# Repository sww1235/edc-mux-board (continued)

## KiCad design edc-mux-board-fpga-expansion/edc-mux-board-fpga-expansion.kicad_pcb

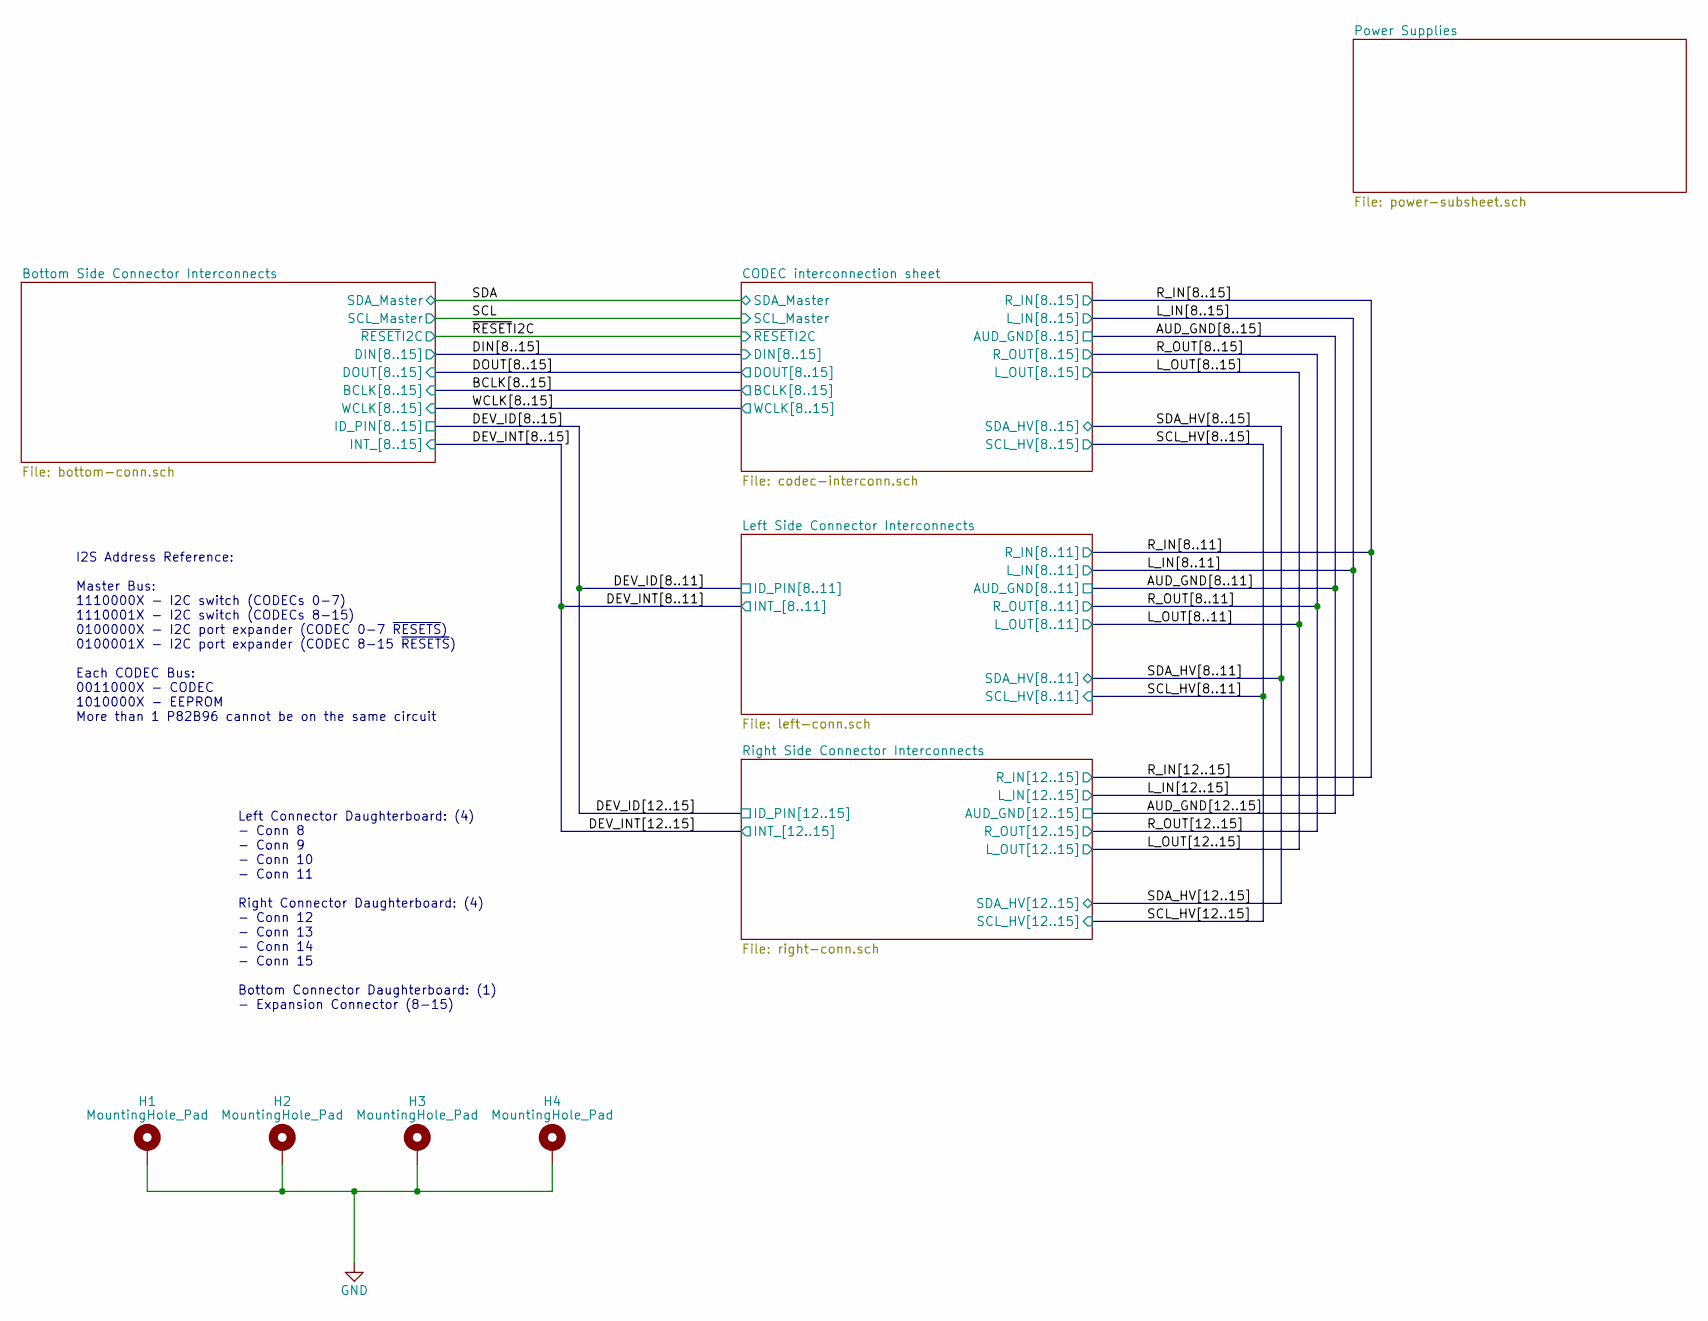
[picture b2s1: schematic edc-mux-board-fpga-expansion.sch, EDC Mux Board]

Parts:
H1, H2, H3, H4: MountingHole_Pad; MountingHole_4.3mm_M4_Pad_Via

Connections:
GND: H1.1, H2.1, H3.1, H4.1; also elsewhere on the board

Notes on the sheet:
Left Connector Daughterboard: (4) - Conn 8 - Conn 9 - Conn 10 - Conn 11 Right Connector Daughterboard: (4) - Conn 12 - Conn 13 - Conn 14 - Conn 15 Bottom Connector Daughterboard: (1) - Expansion Connector (8-15)
I2S Address Reference: Master Bus: 1110000X - I2C switch (CODECs 0-7) 1110001X - I2C switch (CODECs 8-15) 0100000X - I2C port expander (CODEC 0-7 ~RESETS~) 0100001X - I2C port expander (CODEC 8-15 ~RESETS~) Each CODEC Bus: 0011000X - CODEC 1010000X - EEPROM More than 1 P82B96 cannot be on the same 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

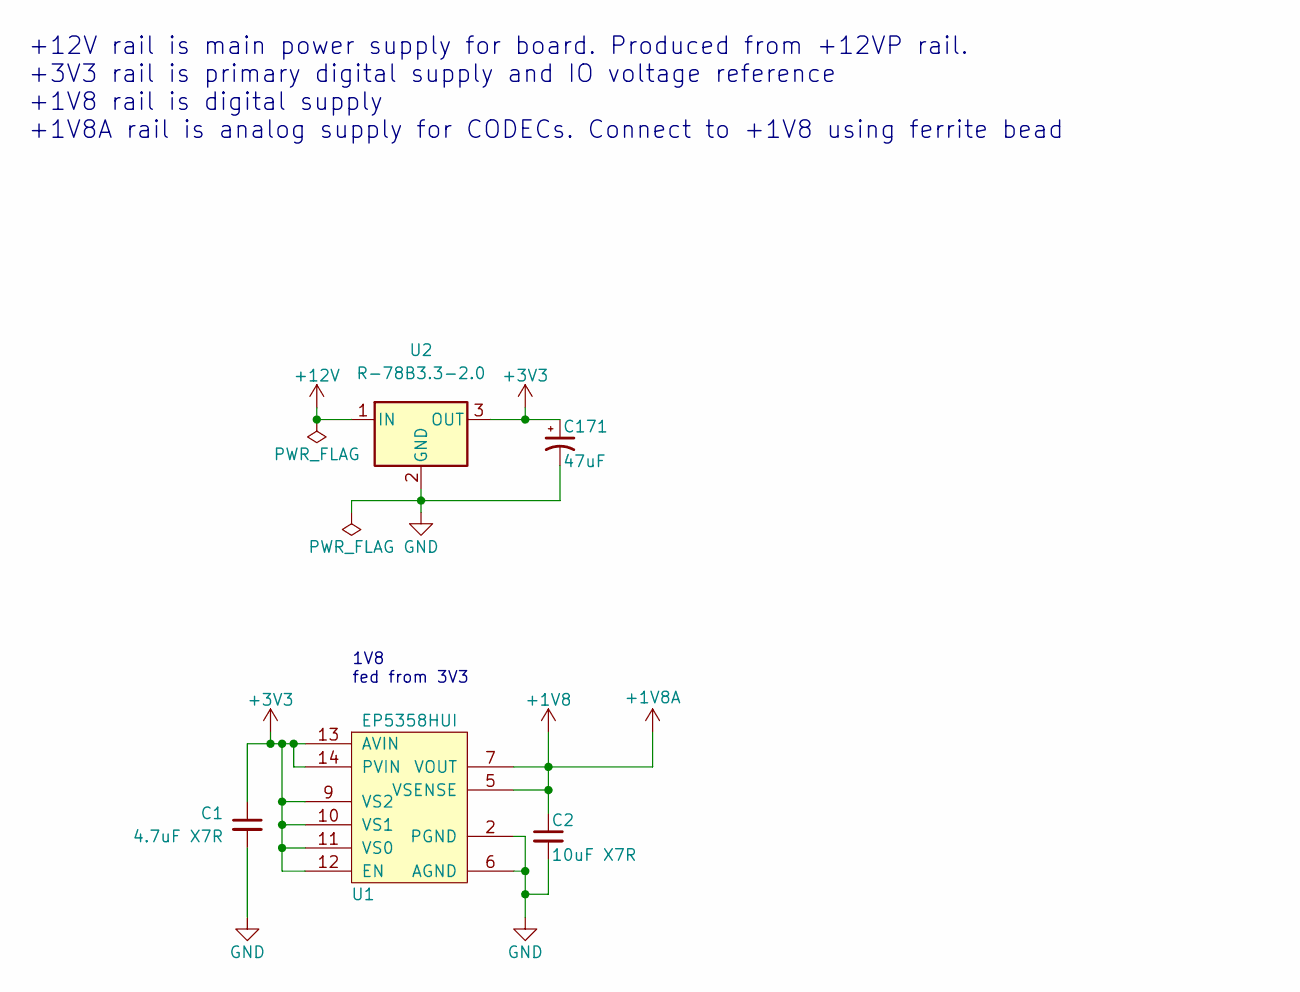
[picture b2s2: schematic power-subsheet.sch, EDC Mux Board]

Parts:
C1: 4.7uF X7R; C_0805_2012Metric; Manufacturers Part Numb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 C2012X7R1E475K125AB
C2: 10uF X7R; C_1206_3216Metric; Manufacturers Part Numb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 C1206C106J3RACAUTO
C171: 47uF; CP_ELEC_8.3x8.3x11.7mm_SMD; Manufacturers Part Numb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 875075555002
U1: EP5358HUI; ENPIRION_QFN16_2.5x2.25x1.1mm-0.4mm; Manufacturers Part Numb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 EP5358HUI
U2: R-78B3.3-2.0; Converter_DCDC_RECOM_R-78B-2.0_THT; Manufacturers Part Numb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 R-78B3.3-2.0

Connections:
+1V8: C2.1, U1.5 (VSENSE), U1.7 (VOUT), U1.8 (VOUT); also elsewhere on the board
+3V3: C1.1, C171.1, U1.9 (VS2), U1.10 (VS1), U1.11 (VS0), U1.12 (EN), U1.13 (AVIN), U1.14 (PVIN), U2.3 (OUT); also elsewhere on the board
+12V: U2.1 (IN); also elsewhere on the board
GND: C1.2, C2.2, C171.2, U1.2 (PGND), U1.3 (PGND), U1.6 (AGND), U2.2 (GND); also elsewhere on the board

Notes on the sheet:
+12V rail is main power supply for board. Produced from +12VP rail. +3V3 rail is primary digital supply and IO voltage reference +1V8 rail is digital supply +1V8A rail is analog supply for CODECs. Connect to +1V8 using ferrite bead
1V8 fed from 3V3

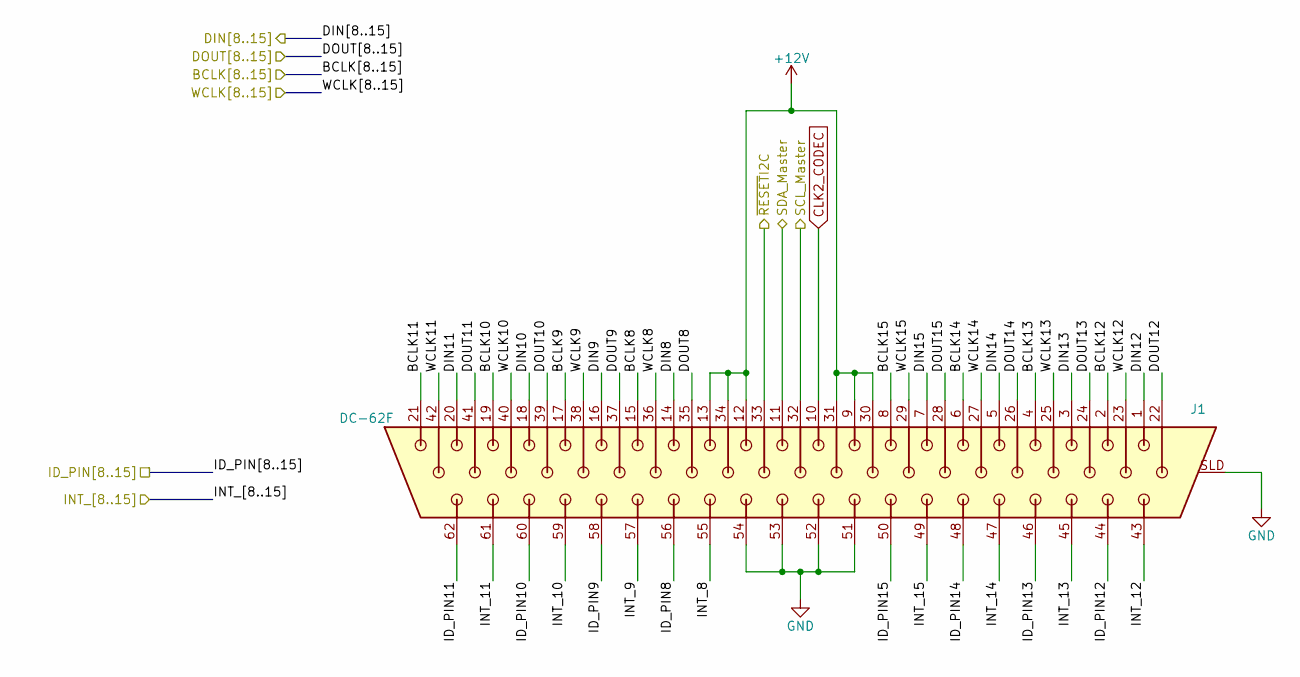
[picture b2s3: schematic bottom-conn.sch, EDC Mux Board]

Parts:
J1: DC-62F; 09564525612; Manufacturers Part Numb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 09564525612

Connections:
+12V: J1.9, J1.12, J1.13, J1.30, J1.31, J1.34; also elsewhere on the board
/Bottom Side Connector Interconnects/BCLK8: J1.15; also elsewhere on the board
/Bottom Side Connector Interconnects/BCLK9: J1.17; also elsewhere on the board
/Bottom Side Connector Interconnects/BCLK10: J1.19; also elsewhere on the board
/Bottom Side Connector Interconnects/BCLK11: J1.21; also elsewhere on the board
/Bottom Side Connector Interconnects/BCLK12: J1.2; also elsewhere on the board
/Bottom Side Connector Interconnects/BCLK13: J1.4; also elsewhere on the board
/Bottom Side Connector Interconnects/BCLK14: J1.6; also elsewhere on the board
/Bottom Side Connector Interconnects/BCLK15: J1.8; also elsewhere on the board
/Bottom Side Connector Interconnects/DIN8: J1.14; also elsewhere on the board
/Bottom Side Connector Interconnects/DIN9: J1.16; also elsewhere on the board
/Bottom Side Connector Interconnects/DIN10: J1.18; also elsewhere on the board
/Bottom Side Connector Interconnects/DIN11: J1.20; also elsewhere on the board
/Bottom Side Connector Interconnects/DIN12: J1.1; also elsewhere on the board
/Bottom Side Connector Interconnects/DIN13: J1.3; also elsewhere on the board
/Bottom Side Connector Interconnects/DIN14: J1.5; also elsewhere on the board
/Bottom Side Connector Interconnects/DIN15: J1.7; also elsewhere on the board
/Bottom Side Connector Interconnects/DOUT8: J1.35; also elsewhere on the board
/Bottom Side Connector Interconnects/DOUT9: J1.37; also elsewhere on the board
/Bottom Side Connector Interconnects/DOUT10: J1.39; also elsewhere on the board
/Bottom Side Connector Interconnects/DOUT11: J1.41; also elsewhere on the board
/Bottom Side Connector Interconnects/DOUT12: J1.22; also elsewhere on the board
/Bottom Side Connector Interconnects/DOUT13: J1.24; also elsewhere on the board
/Bottom Side Connector Interconnects/DOUT14: J1.26; also elsewhere on the board
/Bottom Side Connector Interconnects/DOUT15: J1.28; also elsewhere on the board
/Bottom Side Connector Interconnects/ID_PIN8: J1.56; also elsewhere on the board
/Bottom Side Connector Interconnects/ID_PIN9: J1.58; also elsewhere on the board
/Bottom Side Connector Interconnects/ID_PIN10: J1.60; also elsewhere on the board
/Bottom Side Connector Interconnects/ID_PIN11: J1.62; also elsewhere on the board
/Bottom Side Connector Interconnects/ID_PIN12: J1.44; also elsewhere on the board
/Bottom Side Connector Interconnects/ID_PIN13: J1.46; also elsewhere on the board
/Bottom Side Connector Interconnects/ID_PIN14: J1.48; also elsewhere on the board
/Bottom Side Connector Interconnects/ID_PIN15: J1.50; also elsewhere on the board
/Bottom Side Connector Interconnects/INT_8: J1.55; also elsewhere on the board
/Bottom Side Connector Interconnects/INT_9: J1.57; also elsewhere on the board
/Bottom Side Connector Interconnects/INT_10: J1.59; also elsewhere on the board
/Bottom Side Connector Interconnects/INT_11: J1.61; also elsewhere on the board
/Bottom Side Connector Interconnects/INT_12: J1.43; also elsewhere on the board
/Bottom Side Connector Interconnects/INT_13: J1.45; also elsewhere on the board
/Bottom Side Connector Interconnects/INT_14: J1.47; also elsewhere on the board
/Bottom Side Connector Interconnects/INT_15: J1.49; also elsewhere on the board
/Bottom Side Connector Interconnects/WCLK8: J1.36; also elsewhere on the board
/Bottom Side Connector Interconnects/WCLK9: J1.38; also elsewhere on the board
/Bottom Side Connector Interconnects/WCLK10: J1.40; also elsewhere on the board
/Bottom Side Connector Interconnects/WCLK11: J1.42; also elsewhere on the board
/Bottom Side Connector Interconnects/WCLK12: J1.23; also elsewhere on the board
/Bottom Side Connector Interconnects/WCLK13: J1.25; also elsewhere on the board
/Bottom Side Connector Interconnects/WCLK14: J1.27; also elsewhere on the board
/Bottom Side Connector Interconnects/WCLK15: J1.29; also elsewhere on the board
/SCL: J1.32; also elsewhere on the board
/SDA: J1.11; also elsewhere on the board
/~RESET~I2C: J1.33; also elsewhere on the board
CLK2_CODEC: J1.10; also elsewhere on the board
GND: J1.51, J1.52, J1.53, J1.54, J1.SLD (SHIELD); also elsewhere on the board

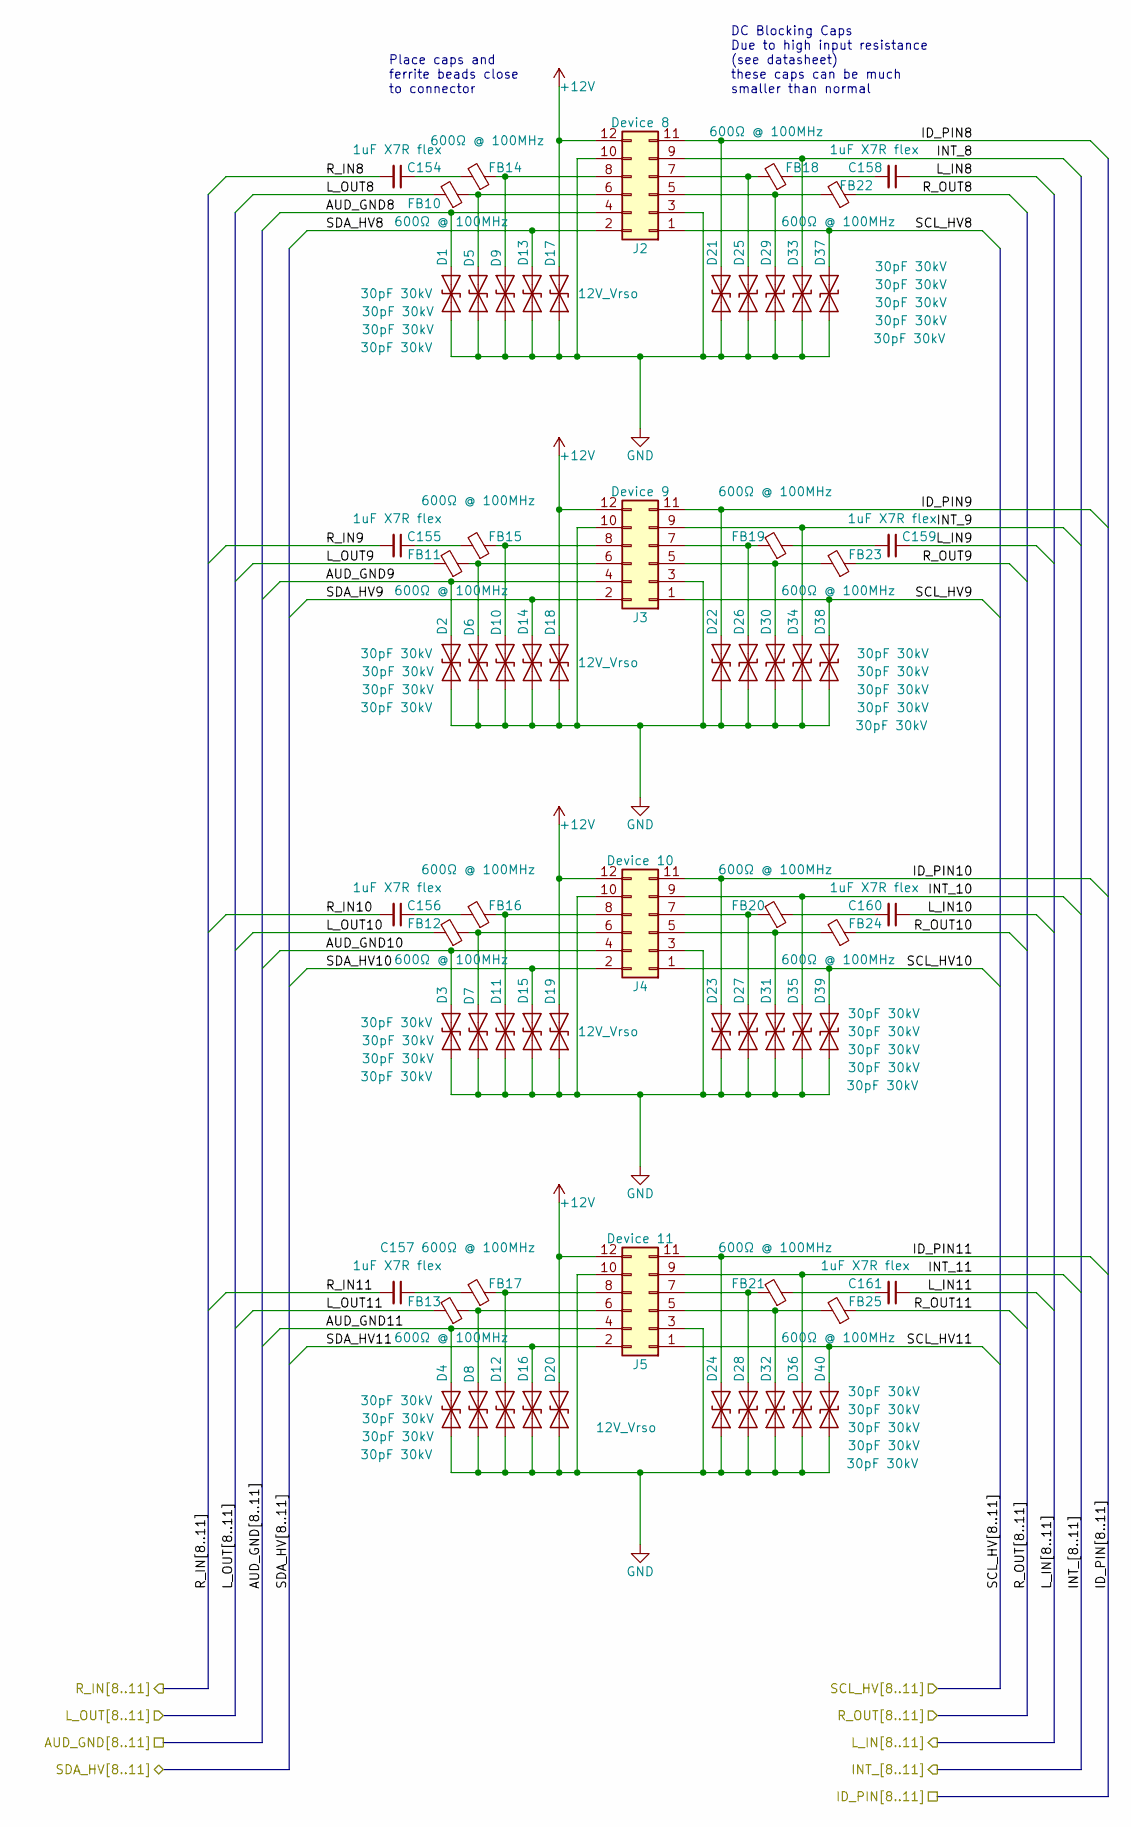
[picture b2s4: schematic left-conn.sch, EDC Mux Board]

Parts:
C154, C155, C156, C157, C158, C159, C160, C161: 1uF X7R flex; C_0805_2012Metric; Manufacturers Part Numb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 C0805X105J3RECAUTO
D1, D2, D3, D4, D5, D6, D7, D8, D9, D10, D11, D12, D13, D14, D15, D16, D21, D22, D23, D24, D25, D26, D27, D28, D29, D30, D31, D32, D33, D34, D35, D36, D37, D38, D39, D40: 30pF 30kV; D_0402_1005Metric; Manufacturers Part Numb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 SP1005-01ETG
D17, D18, D19, D20: 12V_Vrso; D_SMA; Manufacturers Part Numb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 SMAJ12CA
FB10, FB11, FB12, FB13, FB14, FB15, FB16, FB17, FB18, FB19, FB20, FB21, FB22, FB23, FB24, FB25: 600Ω @ 100MHz; L_0805_2012Metric; Manufacturers Part Numb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 BLM21AG601SZ1D
J2: Device 8; JST_PHD_B12B-PHDSS_2x06_P2.00mm_Vertical; Manufacturers Part Numb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 B12B-PHDSS(LF)(SN)
J3: Device 9; JST_PHD_B12B-PHDSS_2x06_P2.00mm_Vertical; Manufacturers Part Numb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 B12B-PHDSS(LF)(SN)
J4: Device 10; JST_PHD_B12B-PHDSS_2x06_P2.00mm_Vertical; Manufacturers Part Numb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 B12B-PHDSS(LF)(SN)
J5: Device 11; JST_PHD_B12B-PHDSS_2x06_P2.00mm_Vertical; Manufacturers Part Numb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 B12B-PHDSS(LF)(SN)

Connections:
+12V: D17.1 (A1), D18.1 (A1), D19.1 (A1), D20.1 (A1), J2.12, J3.12, J4.12, J5.12; also elsewhere on the board
/Bottom Side Connector Interconnects/ID_PIN8: D21.1 (A1), J2.11; also elsewhere on the board
/Bottom Side Connector Interconnects/ID_PIN9: D22.1 (A1), J3.11; also elsewhere on the board
/Bottom Side Connector Interconnects/ID_PIN10: D23.1 (A1), J4.11; also elsewhere on the board
/Bottom Side Connector Interconnects/ID_PIN11: D24.1 (A1), J5.11; also elsewhere on the board
/Bottom Side Connector Interconnects/INT_8: D33.1 (A1), J2.9; also elsewhere on the board
/Bottom Side Connector Interconnects/INT_9: D34.1 (A1), J3.9; also elsewhere on the board
/Bottom Side Connector Interconnects/INT_10: D35.1 (A1), J4.9; also elsewhere on the board
/Bottom Side Connector Interconnects/INT_11: D36.1 (A1), J5.9; also elsewhere on the board
/CODEC interconnection sheet/AUD_GND8: D1.1 (A1), J2.4; also elsewhere on the board
/CODEC interconnection sheet/AUD_GND9: D2.1 (A1), J3.4; also elsewhere on the board
/CODEC interconnection sheet/AUD_GND10: D3.1 (A1), J4.4; also elsewhere on the board
/CODEC interconnection sheet/AUD_GND11: D4.1 (A1), J5.4; also elsewhere on the board
/CODEC interconnection sheet/L_IN8: C158.1; also elsewhere on the board
/CODEC interconnection sheet/L_IN9: C159.1; also elsewhere on the board
/CODEC interconnection sheet/L_IN10: C160.1; also elsewhere on the board
/CODEC interconnection sheet/L_IN11: C161.1; also elsewhere on the board
/CODEC interconnection sheet/L_OUT8: FB10.2; also elsewhere on the board
/CODEC interconnection sheet/L_OUT9: FB11.2; also elsewhere on the board
/CODEC interconnection sheet/L_OUT10: FB12.2; also elsewhere on the board
/CODEC interconnection sheet/L_OUT11: FB13.2; also elsewhere on the board
/CODEC interconnection sheet/R_IN8: C154.2; also elsewhere on the board
/CODEC interconnection sheet/R_IN9: C155.2; also elsewhere on the board
/CODEC interconnection sheet/R_IN10: C156.2; also elsewhere on the board
/CODEC interconnection sheet/R_IN11: C157.2; also elsewhere on the board
/CODEC interconnection sheet/R_OUT8: FB22.1; also elsewhere on the board
/CODEC interconnection sheet/R_OUT9: FB23.1; also elsewhere on the board
/CODEC interconnection sheet/R_OUT10: FB24.1; also elsewhere on the board
/CODEC interconnection sheet/R_OUT11: FB25.1; also elsewhere on the board
/CODEC interconnection sheet/SCL_HV8: D37.1 (A1), J2.1; also elsewhere on the board
/CODEC interconnection sheet/SCL_HV9: D38.1 (A1), J3.1; also elsewhere on the board
/CODEC interconnection sheet/SCL_HV10: D39.1 (A1), J4.1; also elsewhere on the board
/CODEC interconnection sheet/SCL_HV11: D40.1 (A1), J5.1; also elsewhere on the board
/CODEC interconnection sheet/SDA_HV8: D13.1 (A1), J2.2; also elsewhere on the board
/CODEC interconnection sheet/SDA_HV9: D14.1 (A1), J3.2; also elsewhere on the board
/CODEC interconnection sheet/SDA_HV10: D15.1 (A1), J4.2; also elsewhere on the board
/CODEC interconnection sheet/SDA_HV11: D16.1 (A1), J5.2; also elsewhere on the board
GND: D1.2 (A2), D2.2 (A2), D3.2 (A2), D4.2 (A2), D5.2 (A2), D6.2 (A2), D7.2 (A2), D8.2 (A2), D9.2 (A2), D10.2 (A2), D11.2 (A2), D12.2 (A2), D13.2 (A2), D14.2 (A2), D15.2 (A2), D16.2 (A2), D17.2 (A2), D18.2 (A2), D19.2 (A2), D20.2 (A2), D21.2 (A2), D22.2 (A2), D23.2 (A2), D24.2 (A2), D25.2 (A2), D26.2 (A2), D27.2 (A2), D28.2 (A2), D29.2 (A2), D30.2 (A2), D31.2 (A2), D32.2 (A2), D33.2 (A2), D34.2 (A2), D35.2 (A2), D36.2 (A2), D37.2 (A2), D38.2 (A2), D39.2 (A2), D40.2 (A2), J2.3, J2.10, J3.3, J3.10, J4.3, J4.10, J5.3, J5.10; also elsewhere on the board
unnamed: C154.1, FB14.2
unnamed: C155.1, FB15.2
unnamed: C156.1, FB16.2
unnamed: C157.1, FB17.2
unnamed: C158.2, FB18.1
unnamed: C159.2, FB19.1
unnamed: C160.2, FB20.1
unnamed: C161.2, FB21.1
unnamed: D5.1 (A1), FB10.1, J2.6
unnamed: D6.1 (A1), FB11.1, J3.6
unnamed: D7.1 (A1), FB12.1, J4.6
unnamed: D8.1 (A1), FB13.1, J5.6
unnamed: D9.1 (A1), FB14.1, J2.8
unnamed: D10.1 (A1), FB15.1, J3.8
unnamed: D11.1 (A1), FB16.1, J4.8
unnamed: D12.1 (A1), FB17.1, J5.8
unnamed: D25.1 (A1), FB18.2, J2.7
unnamed: D26.1 (A1), FB19.2, J3.7
unnamed: D27.1 (A1), FB20.2, J4.7
unnamed: D28.1 (A1), FB21.2, J5.7
unnamed: D29.1 (A1), FB22.2, J2.5
unnamed: D30.1 (A1), FB23.2, J3.5
unnamed: D31.1 (A1), FB24.2, J4.5
unnamed: D32.1 (A1), FB25.2, J5.5

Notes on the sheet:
DC Blocking Caps Due to high input resistance (see datasheet) these caps can be much smaller than normal
Place caps and ferrite beads close to connector

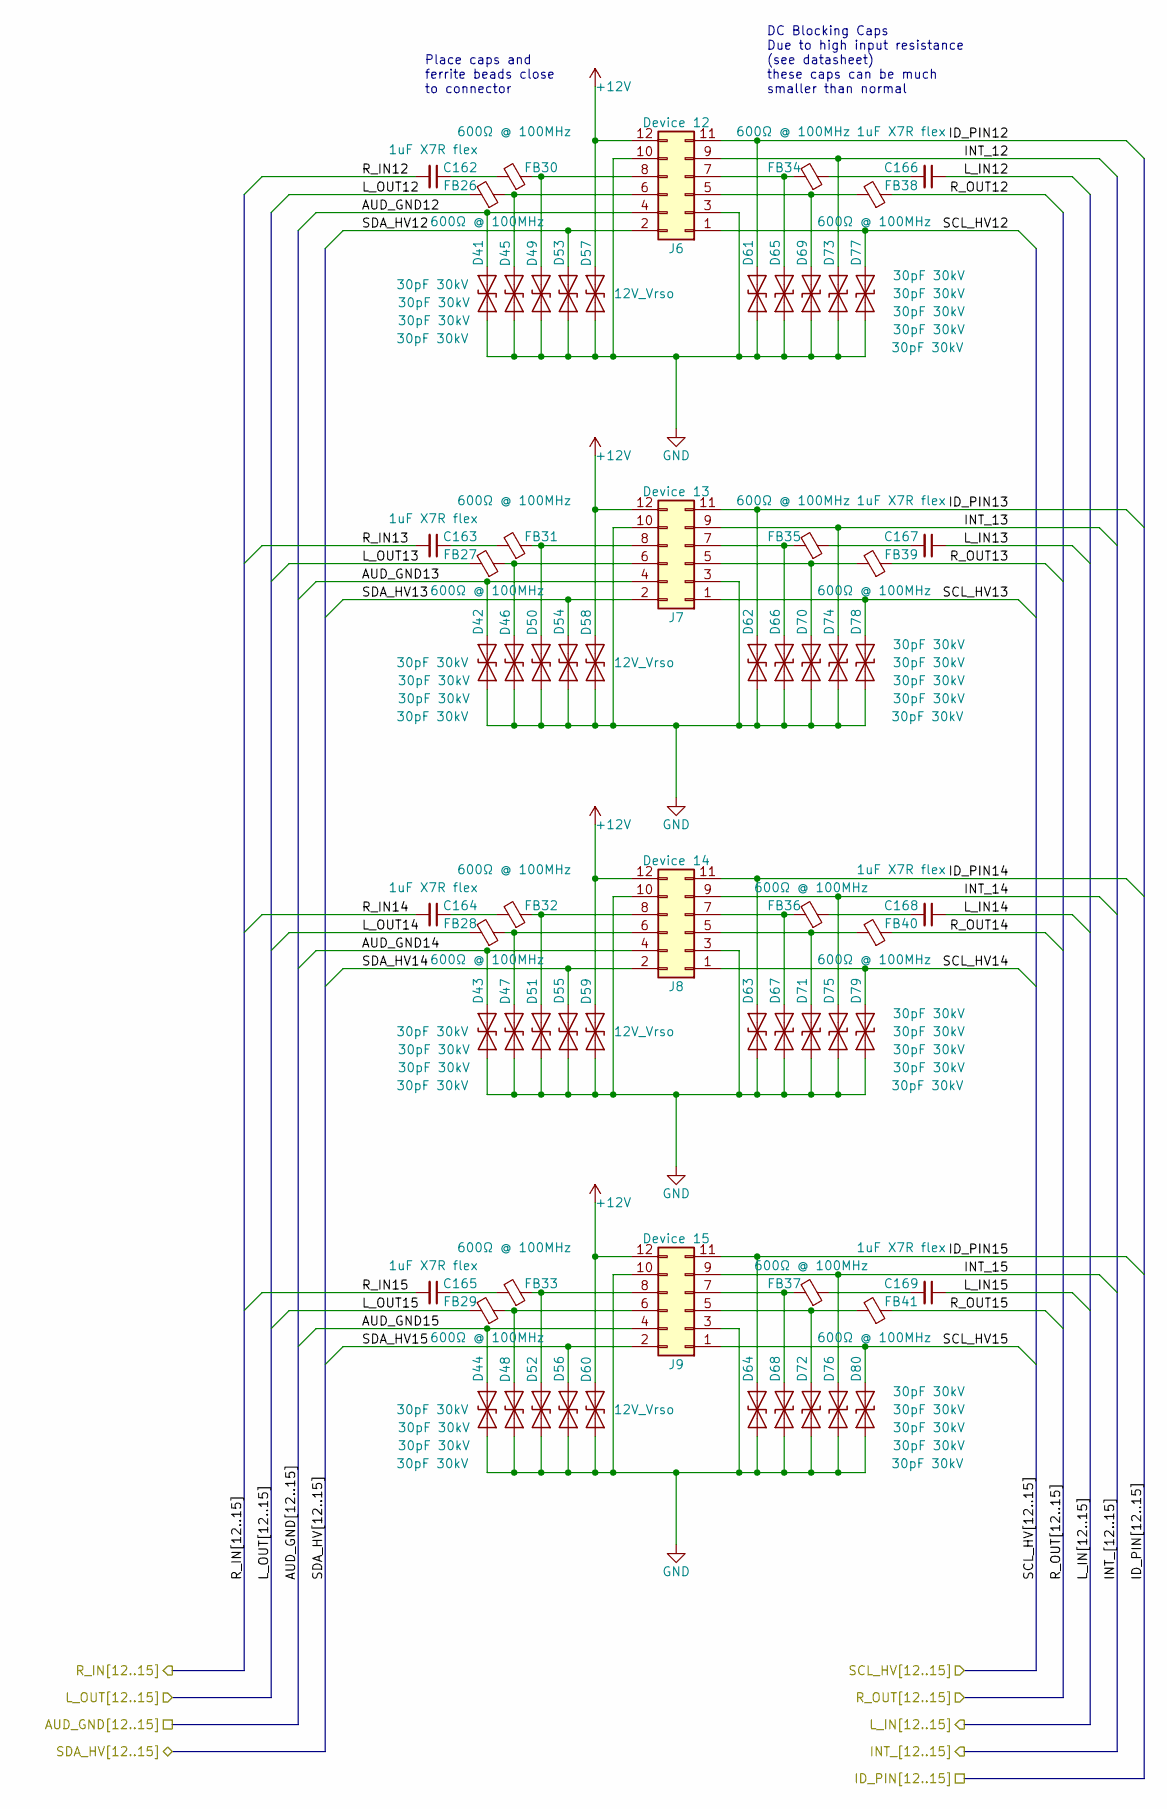
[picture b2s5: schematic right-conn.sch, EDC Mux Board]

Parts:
C162, C163, C164, C165, C166, C167, C168, C169: 1uF X7R flex; C_0805_2012Metric; Manufacturers Part Numb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 C0805X105J3RECAUTO
D41, D42, D43, D44, D45, D46, D47, D48, D49, D50, D51, D52, D53, D54, D55, D56, D61, D62, D63, D64, D65, D66, D67, D68, D69, D70, D71, D72, D73, D74, D75, D76, D77, D78, D79, D80: 30pF 30kV; D_0402_1005Metric; Manufacturers Part Numb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 SP1005-01ETG
D57, D58, D59, D60: 12V_Vrso; D_SMA; Manufacturers Part Numb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 SMAJ12CA
FB26, FB27, FB28, FB29, FB30, FB31, FB32, FB33, FB34, FB35, FB36, FB37, FB38, FB39, FB40, FB41: 600Ω @ 100MHz; L_0805_2012Metric; Manufacturers Part Numb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 BLM21AG601SZ1D
J6: Device 12; JST_PHD_B12B-PHDSS_2x06_P2.00mm_Vertical; Manufacturers Part Numb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 B12B-PHDSS(LF)(SN)
J7: Device 13; JST_PHD_B12B-PHDSS_2x06_P2.00mm_Vertical; Manufacturers Part Numb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 B12B-PHDSS(LF)(SN)
J8: Device 14; JST_PHD_B12B-PHDSS_2x06_P2.00mm_Vertical; Manufacturers Part Numb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 B12B-PHDSS(LF)(SN)
J9: Device 15; JST_PHD_B12B-PHDSS_2x06_P2.00mm_Vertical; Manufacturers Part Numb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 B12B-PHDSS(LF)(SN)

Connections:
+12V: D57.1 (A1), D58.1 (A1), D59.1 (A1), D60.1 (A1), J6.12, J7.12, J8.12, J9.12; also elsewhere on the board
/Bottom Side Connector Interconnects/ID_PIN12: D61.1 (A1), J6.11; also elsewhere on the board
/Bottom Side Connector Interconnects/ID_PIN13: D62.1 (A1), J7.11; also elsewhere on the board
/Bottom Side Connector Interconnects/ID_PIN14: D63.1 (A1), J8.11; also elsewhere on the board
/Bottom Side Connector Interconnects/ID_PIN15: D64.1 (A1), J9.11; also elsewhere on the board
/Bottom Side Connector Interconnects/INT_12: D73.1 (A1), J6.9; also elsewhere on the board
/Bottom Side Connector Interconnects/INT_13: D74.1 (A1), J7.9; also elsewhere on the board
/Bottom Side Connector Interconnects/INT_14: D75.1 (A1), J8.9; also elsewhere on the board
/Bottom Side Connector Interconnects/INT_15: D76.1 (A1), J9.9; also elsewhere on the board
/CODEC interconnection sheet/AUD_GND12: D41.1 (A1), J6.4; also elsewhere on the board
/CODEC interconnection sheet/AUD_GND13: D42.1 (A1), J7.4; also elsewhere on the board
/CODEC interconnection sheet/AUD_GND14: D43.1 (A1), J8.4; also elsewhere on the board
/CODEC interconnection sheet/AUD_GND15: D44.1 (A1), J9.4; also elsewhere on the board
/CODEC interconnection sheet/L_IN12: C166.1; also elsewhere on the board
/CODEC interconnection sheet/L_IN13: C167.1; also elsewhere on the board
/CODEC interconnection sheet/L_IN14: C168.1; also elsewhere on the board
/CODEC interconnection sheet/L_IN15: C169.1; also elsewhere on the board
/CODEC interconnection sheet/L_OUT12: FB26.2; also elsewhere on the board
/CODEC interconnection sheet/L_OUT13: FB27.2; also elsewhere on the board
/CODEC interconnection sheet/L_OUT14: FB28.2; also elsewhere on the board
/CODEC interconnection sheet/L_OUT15: FB29.2; also elsewhere on the board
/CODEC interconnection sheet/R_IN12: C162.2; also elsewhere on the board
/CODEC interconnection sheet/R_IN13: C163.2; also elsewhere on the board
/CODEC interconnection sheet/R_IN14: C164.2; also elsewhere on the board
/CODEC interconnection sheet/R_IN15: C165.2; also elsewhere on the board
/CODEC interconnection sheet/R_OUT12: FB38.1; also elsewhere on the board
/CODEC interconnection sheet/R_OUT13: FB39.1; also elsewhere on the board
/CODEC interconnection sheet/R_OUT14: FB40.1; also elsewhere on the board
/CODEC interconnection sheet/R_OUT15: FB41.1; also elsewhere on the board
/CODEC interconnection sheet/SCL_HV12: D77.1 (A1), J6.1; also elsewhere on the board
/CODEC interconnection sheet/SCL_HV13: D78.1 (A1), J7.1; also elsewhere on the board
/CODEC interconnection sheet/SCL_HV14: D79.1 (A1), J8.1; also elsewhere on the board
/CODEC interconnection sheet/SCL_HV15: D80.1 (A1), J9.1; also elsewhere on the board
/CODEC interconnection sheet/SDA_HV12: D53.1 (A1), J6.2; also elsewhere on the board
/CODEC interconnection sheet/SDA_HV13: D54.1 (A1), J7.2; also elsewhere on the board
/CODEC interconnection sheet/SDA_HV14: D55.1 (A1), J8.2; also elsewhere on the board
/CODEC interconnection sheet/SDA_HV15: D56.1 (A1), J9.2; also elsewhere on the board
GND: D41.2 (A2), D42.2 (A2), D43.2 (A2), D44.2 (A2), D45.2 (A2), D46.2 (A2), D47.2 (A2), D48.2 (A2), D49.2 (A2), D50.2 (A2), D51.2 (A2), D52.2 (A2), D53.2 (A2), D54.2 (A2), D55.2 (A2), D56.2 (A2), D57.2 (A2), D58.2 (A2), D59.2 (A2), D60.2 (A2), D61.2 (A2), D62.2 (A2), D63.2 (A2), D64.2 (A2), D65.2 (A2), D66.2 (A2), D67.2 (A2), D68.2 (A2), D69.2 (A2), D70.2 (A2), D71.2 (A2), D72.2 (A2), D73.2 (A2), D74.2 (A2), D75.2 (A2), D76.2 (A2), D77.2 (A2), D78.2 (A2), D79.2 (A2), D80.2 (A2), J6.3, J6.10, J7.3, J7.10, J8.3, J8.10, J9.3, J9.10; also elsewhere on the board
unnamed: C162.1, FB30.2
unnamed: C163.1, FB31.2
unnamed: C164.1, FB32.2
unnamed: C165.1, FB33.2
unnamed: C166.2, FB34.1
unnamed: C167.2, FB35.1
unnamed: C168.2, FB36.1
unnamed: C169.2, FB37.1
unnamed: D45.1 (A1), FB26.1, J6.6
unnamed: D46.1 (A1), FB27.1, J7.6
unnamed: D47.1 (A1), FB28.1, J8.6
unnamed: D48.1 (A1), FB29.1, J9.6
unnamed: D49.1 (A1), FB30.1, J6.8
unnamed: D50.1 (A1), FB31.1, J7.8
unnamed: D51.1 (A1), FB32.1, J8.8
unnamed: D52.1 (A1), FB33.1, J9.8
unnamed: D65.1 (A1), FB34.2, J6.7
unnamed: D66.1 (A1), FB35.2, J7.7
unnamed: D67.1 (A1), FB36.2, J8.7
unnamed: D68.1 (A1), FB37.2, J9.7
unnamed: D69.1 (A1), FB38.2, J6.5
unnamed: D70.1 (A1), FB39.2, J7.5
unnamed: D71.1 (A1), FB40.2, J8.5
unnamed: D72.1 (A1), FB41.2, J9.5

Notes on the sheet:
DC Blocking Caps Due to high input resistance (see datasheet) these caps can be much smaller than normal
Place caps and ferrite beads close to connector
